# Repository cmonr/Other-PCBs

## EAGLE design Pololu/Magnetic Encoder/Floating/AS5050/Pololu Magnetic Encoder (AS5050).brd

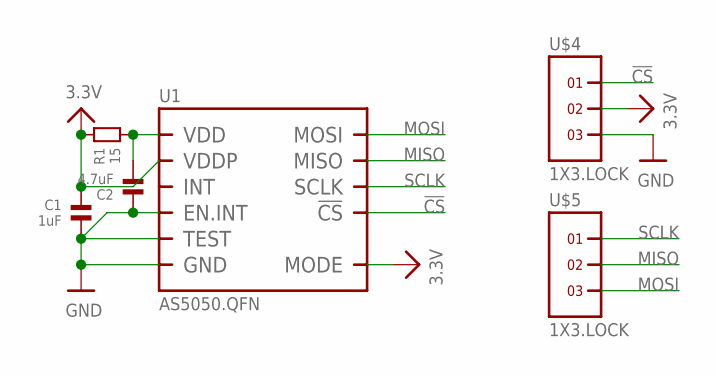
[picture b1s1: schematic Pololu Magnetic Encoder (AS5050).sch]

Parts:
C1: 1uF; 0603
C2: 4.7uF; 0603
R1: 15; 0603
U1: AS5050.QFN; QFN.16
U$4, U$5: 1X3.LOCK

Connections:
3.3V: C1.1, R1.1, U1.11 (VDDP), U1.14 (MODE), U$4.2
!CS: U1.4 (!CS), U$4.1
GND: C1.2, C2.1, U1.9 (TEST), U1.10 (EN.INT), U1.13 (GND), U$4.3
MISO: U1.2 (MISO), U$5.2
MOSI: U1.1 (MOSI), U$5.3
unnamed: C2.2, R1.2, U1.12 (VDD)
SCLK: U1.3 (SCLK), U$5.1

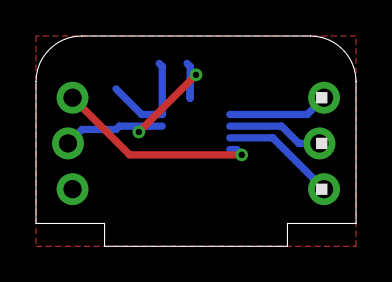
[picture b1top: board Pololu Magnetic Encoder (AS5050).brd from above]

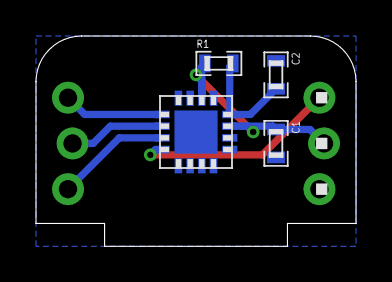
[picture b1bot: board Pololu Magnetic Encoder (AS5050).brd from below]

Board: 2 copper layers, 17.8 x 11.7 mm, 6 parts (5 on the bottom side), 7 nets.

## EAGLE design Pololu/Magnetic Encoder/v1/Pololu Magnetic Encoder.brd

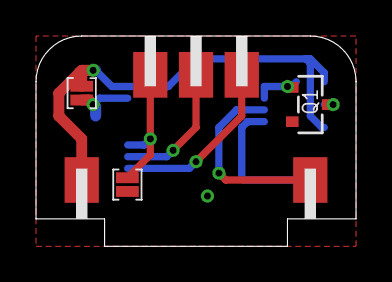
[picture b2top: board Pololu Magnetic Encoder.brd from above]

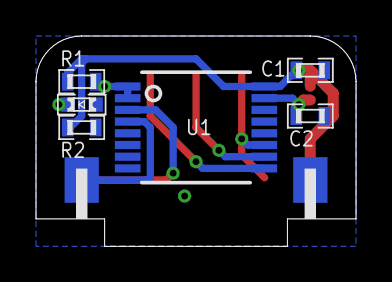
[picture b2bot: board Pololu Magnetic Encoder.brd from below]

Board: 2 copper layers, 17.8 x 11.7 mm, 12 parts (6 on the bottom side), 11 nets.

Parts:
C1: .1uF; 0603
C2: 2.2uF; 0603
J1, J2: 2.LRG.PASTE
LED1: 0603.LED
Q1: SOT23-R
R1: 100k; 0603
R2: 1k; 0603
U1: AS5035; SSOP16
U$1, U$6: 2X1.SIDE
U$9: 1X3.SIDE

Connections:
!CS: J2.1, U1.11, U$9.1
A: U1.3, U$6.1
B: U1.4, U$6.2
CLK: U1.10, U$9.2
DO: U1.9, U$9.3
GND: C1.2, C2.2, J2.2, Q1.2, U1.7, U$1.2
unnamed: LED1.P$2, Q1.3
unnamed: LED1.P$1, R2.2
unnamed: Q1.1, R1.2, U1.1, U1.2
unnamed: C2.1, J1.1, U1.15
VIN: C1.1, J1.2, R1.1, R2.1, U1.16, U$1.1

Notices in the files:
parts and their libraries:
microbuilder: This work is placed in the public domain, and may be freely used for commercial and non-commercial work with the following conditions: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
